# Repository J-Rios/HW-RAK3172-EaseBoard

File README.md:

# HW-RAK3172-EaseBoard

RAK3172 SoM board KiCAD design to ease evaluation and development of this LoRaWAN module based on STM32WL5 SoC.

## Model

## Schematic

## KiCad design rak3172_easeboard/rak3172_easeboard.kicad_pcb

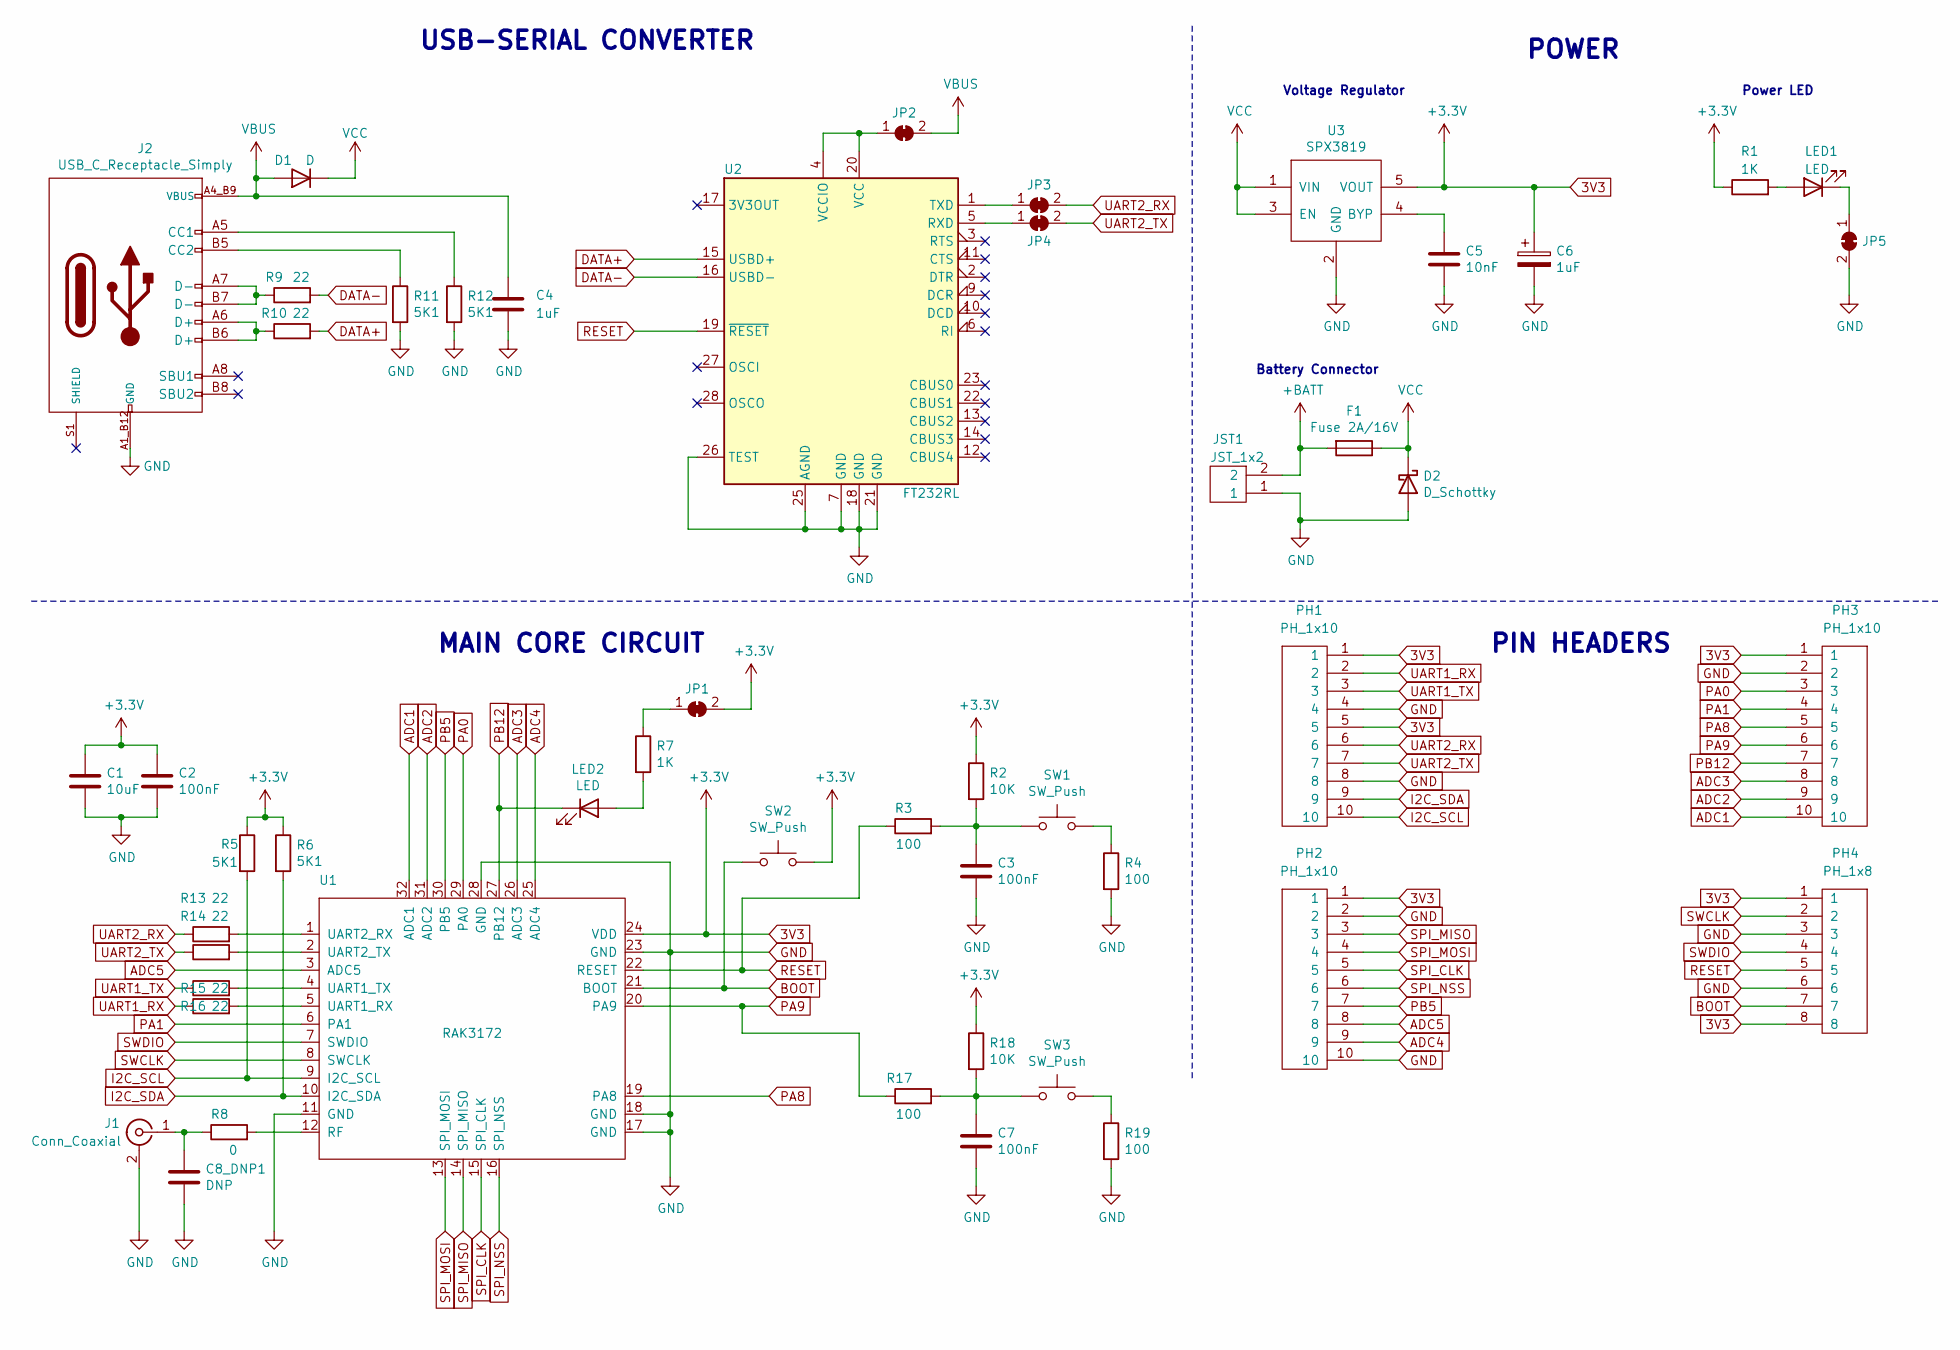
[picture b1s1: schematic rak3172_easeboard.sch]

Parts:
C1: 10uF; C_0805_2012Metric_Pad1.18x1.45mm_HandSolder
C2, C3, C7: 100nF; C_0805_2012Metric_Pad1.18x1.45mm_HandSolder
C4, C6: 1uF; C_0805_2012Metric_Pad1.18x1.45mm_HandSolder
C5: 10nF; C_0805_2012Metric_Pad1.18x1.45mm_HandSolder
C8_DNP1: DNP; C_0805_2012Metric_Pad1.18x1.45mm_HandSolder
D1: D; D_0805_2012Metric_Pad1.15x1.40mm_HandSolder
D2: D_Schottky; D_0805_2012Metric_Pad1.15x1.40mm_HandSolder
F1: Fuse 2A/16V; Fuse_1812_4532Metric_Pad1.30x3.40mm_HandSolder
J1: Conn_Coaxial; SMA_Molex_73251-1153_EdgeMount_Horizontal
J2: USB_C_Receptacle_Simply; USB_C_Receptacle_12
JP1, JP2, JP3, JP4, JP5: SolderJumper_2_Bridged; SolderJumper-2_P1.3mm_Bridged_Pad1.0x1.5mm
JST1: JST_1x2; JST_PH_B2B-PH-K_1x02_P2.00mm_Vertical
LED1, LED2: LED; LED_0805_2012Metric_Pad1.15x1.40mm_HandSolder
PH1, PH2, PH3: PH_1x10; PinHeader_1x10
PH4: PH_1x8; PinHeader_1x8
R1, R7: 1K; R_0805_2012Metric_Pad1.20x1.40mm_HandSolder
R2, R18: 10K; R_0805_2012Metric_Pad1.20x1.40mm_HandSolder
R3, R4, R17, R19: 100; R_0805_2012Metric_Pad1.20x1.40mm_HandSolder
R5, R6, R11, R12: 5K1; R_0805_2012Metric_Pad1.20x1.40mm_HandSolder
R8: 0; R_0805_2012Metric_Pad1.20x1.40mm_HandSolder
R9, R10, R13, R14, R15, R16: 22; R_0805_2012Metric_Pad1.20x1.40mm_HandSolder
SW1, SW2, SW3: SW_Push; SW_Push_1P1T_NO_6x6mm_H9.5mm
U1: RAK3172
U2: FT232RL; SSOP-28_5.3x10.2mm_P0.65mm
U3: SPX3819; TSOT-23-5_HandSoldering

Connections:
3V3: C1.1, C2.1, C6.1, JP1.2 (B), PH1.1, PH1.5, PH2.1, PH3.1, PH4.1, PH4.8, R1.1, R2.1, R5.1, R6.1, R18.1, SW2.2, U1.24 (VDD), U3.5 (VOUT)
+BATT: F1.2, JST1.2
ADC1: PH3.10, U1.32 (ADC1)
ADC2: PH3.9, U1.31 (ADC2)
ADC3: PH3.8, U1.26 (ADC3)
ADC4: PH2.9, U1.25 (ADC4)
ADC5: PH2.8, U1.3 (ADC5)
BOOT: PH4.7, SW2.1, U1.21 (BOOT)
DATA+: R10.2, U2.15 (USBD+)
DATA-: R9.2, U2.16 (USBD-)
GND: C1.2, C2.2, C3.2, C4.2, C5.2, C6.2, C7.2, C8_DNP1.2, D2.2 (A), J1.2 (Ext), J2.A1_B12 (GND), J2.B1_A12 (GND), JP5.2 (B), JST1.1, PH1.4, PH1.8, PH2.2, PH2.10, PH3.2, PH4.3, PH4.6, R4.2, R11.2, R12.2, R19.2, U1.11 (GND), U1.17 (GND), U1.18 (GND), U1.23 (GND), U1.28 (GND), U2.7 (GND), U2.18 (GND), U2.21 (GND), U2.25 (AGND), U2.26 (TEST), U3.2 (GND)
I2C_SCL: PH1.10, R5.2, U1.9 (I2C_SCL)
I2C_SDA: PH1.9, R6.2, U1.10 (I2C_SDA)
unnamed: C3.1, R2.2, R3.2, SW1.1
unnamed: C5.1, U3.4 (BYP)
unnamed: C7.1, R17.2, R18.2, SW3.1
unnamed: C8_DNP1.1, J1.1 (In), R8.1
unnamed: J2.A5 (CC1), R12.1
unnamed: J2.A6 (D+), J2.B6 (D+), R10.1
unnamed: J2.A7 (D-), J2.B7 (D-), R9.1
unnamed: J2.B5 (CC2), R11.1
unnamed: JP1.1 (A), R7.1
unnamed 22: JP2.1 (A), U2.4 (VCCIO), U2.20 (VCC); also elsewhere on the board
unnamed: JP3.1 (A), U2.1 (TXD)
unnamed: JP4.1 (A), U2.5 (RXD)
unnamed: JP5.1 (A), LED1.1 (K)
unnamed: LED1.2 (A), R1.2
unnamed: LED2.2 (A), R7.2
unnamed: R4.1, SW1.2
unnamed: R8.2, U1.12 (RF)
unnamed: R13.2, U1.1 (UART2_RX)
unnamed: R14.2, U1.2 (UART2_TX)
unnamed: R15.2, U1.4 (UART1_TX)
unnamed: R16.2, U1.5 (UART1_RX)
unnamed: R19.1, SW3.2
PA0: PH3.3, U1.29 (PA0)
PA1: PH3.4, U1.6 (PA1)
PA8: PH3.5, U1.19 (PA8)
PA9: PH3.6, R17.1, U1.20 (PA9)
PB5: PH2.7, U1.30 (PB5)
PB12: LED2.1 (K), PH3.7, U1.27 (PB12)
SHIELD: J2.S1 (SHIELD), J2.S2 (SHIELD), J2.S3 (SHIELD), J2.S4 (SHIELD)
SPI_CLK: PH2.5, U1.15 (SPI_CLK)
SPI_MISO: PH2.3, U1.14 (SPI_MISO)
SPI_MOSI: PH2.4, U1.13 (SPI_MOSI)
SPI_NSS: PH2.6, U1.16 (SPI_NSS)
SWCLK: PH4.2, U1.8 (SWCLK)
SWDIO: PH4.4, U1.7 (SWDIO)
UART1_RX: PH1.2, R16.1
UART1_TX: PH1.3, R15.1
UART2_RX: JP3.2 (B), PH1.6, R13.1
UART2_TX: JP4.2 (B), PH1.7, R14.1
VBUS: C4.1, D1.2 (A), J2.A4_B9 (VBUS), J2.B4_A9 (VBUS), JP2.2 (B)
VCC: D1.1 (K), D2.1 (K), F1.1, U3.1 (VIN), U3.3 (EN)

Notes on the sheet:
PIN HEADERS
Power LED
MAIN CORE CIRCUIT
POWER
USB-SERIAL CONVERTER
Battery Connector
Voltage Regulator

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
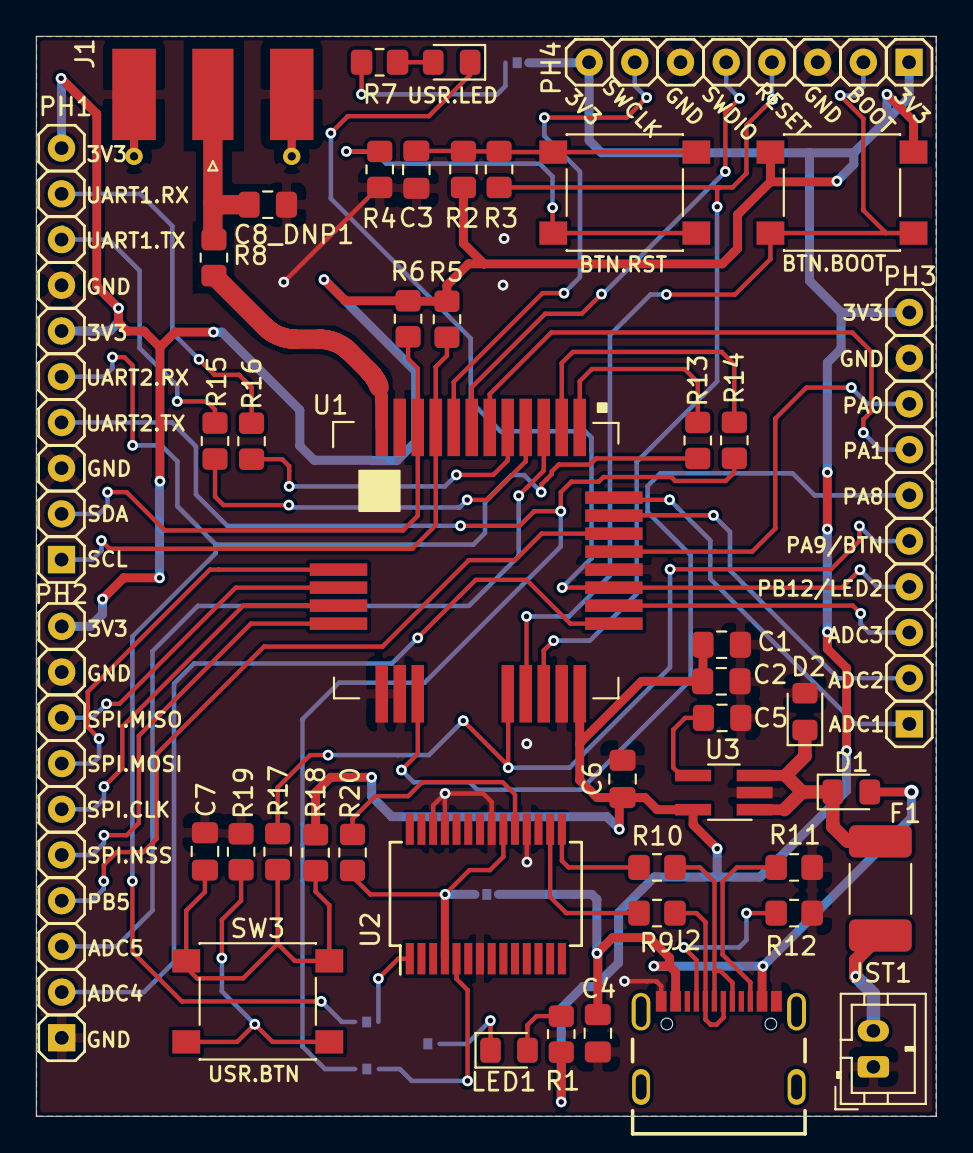
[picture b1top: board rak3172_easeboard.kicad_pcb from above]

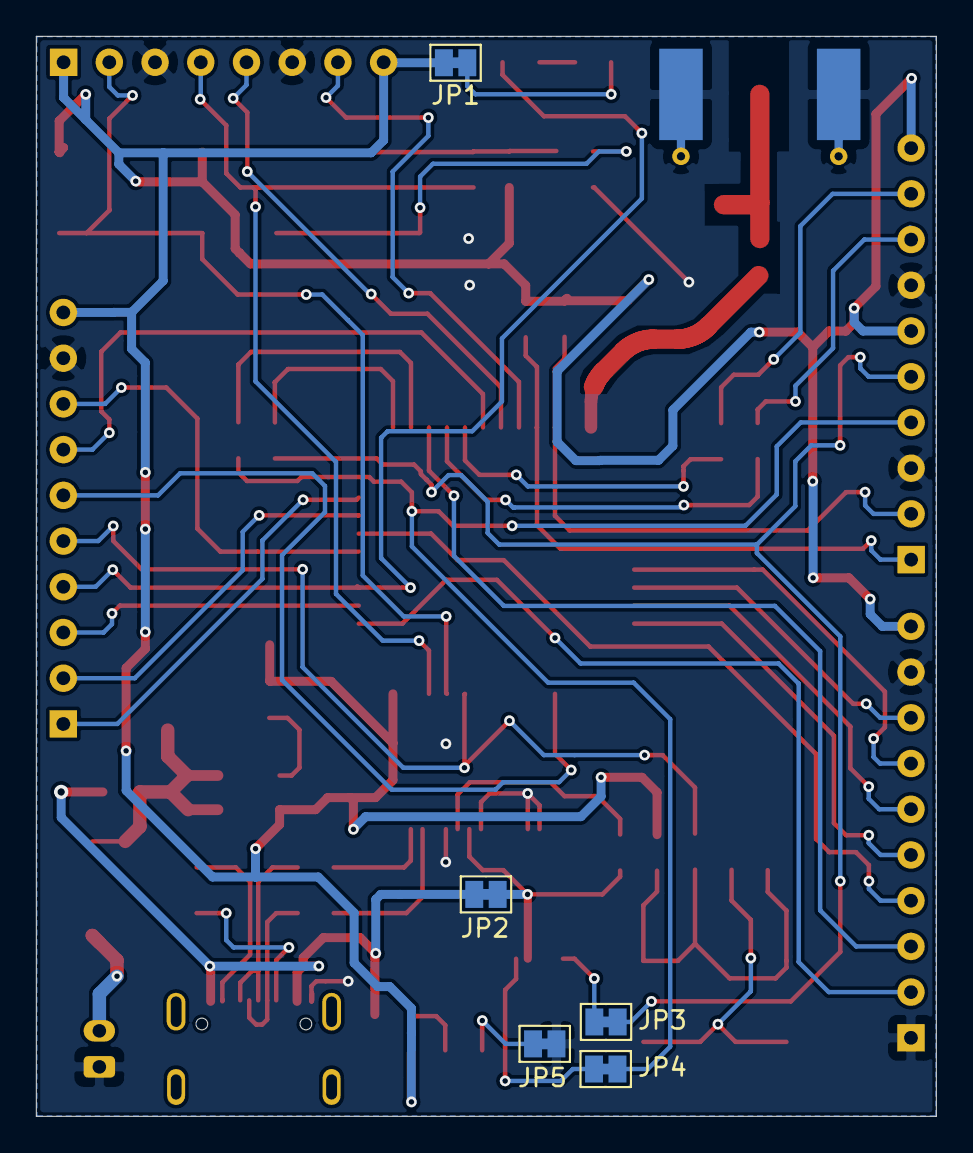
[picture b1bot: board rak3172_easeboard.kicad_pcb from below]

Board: 4 copper layers, 50.0 x 60.0 mm, 51 parts (5 on the bottom side), 56 nets.

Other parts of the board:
R20: 10K; R_0805_2012Metric_Pad1.20x1.40mm_HandSolder

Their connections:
unnamed 22: R20.1; also elsewhere on the board

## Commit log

2021-10-21 Update README file
2021-10-21 Added initial board design
2021-10-31 Update antenna trace. Added BOM
2021-10-31 First release jlcpcb gerbers and drills
2021-10-31 UART serie protection resistors
2021-10-31 Added User Button
2021-10-31 Matching Network
2022-05-03 Disconnect Reset from usb-serial converter
2023-08-18 Added images and show in readme
